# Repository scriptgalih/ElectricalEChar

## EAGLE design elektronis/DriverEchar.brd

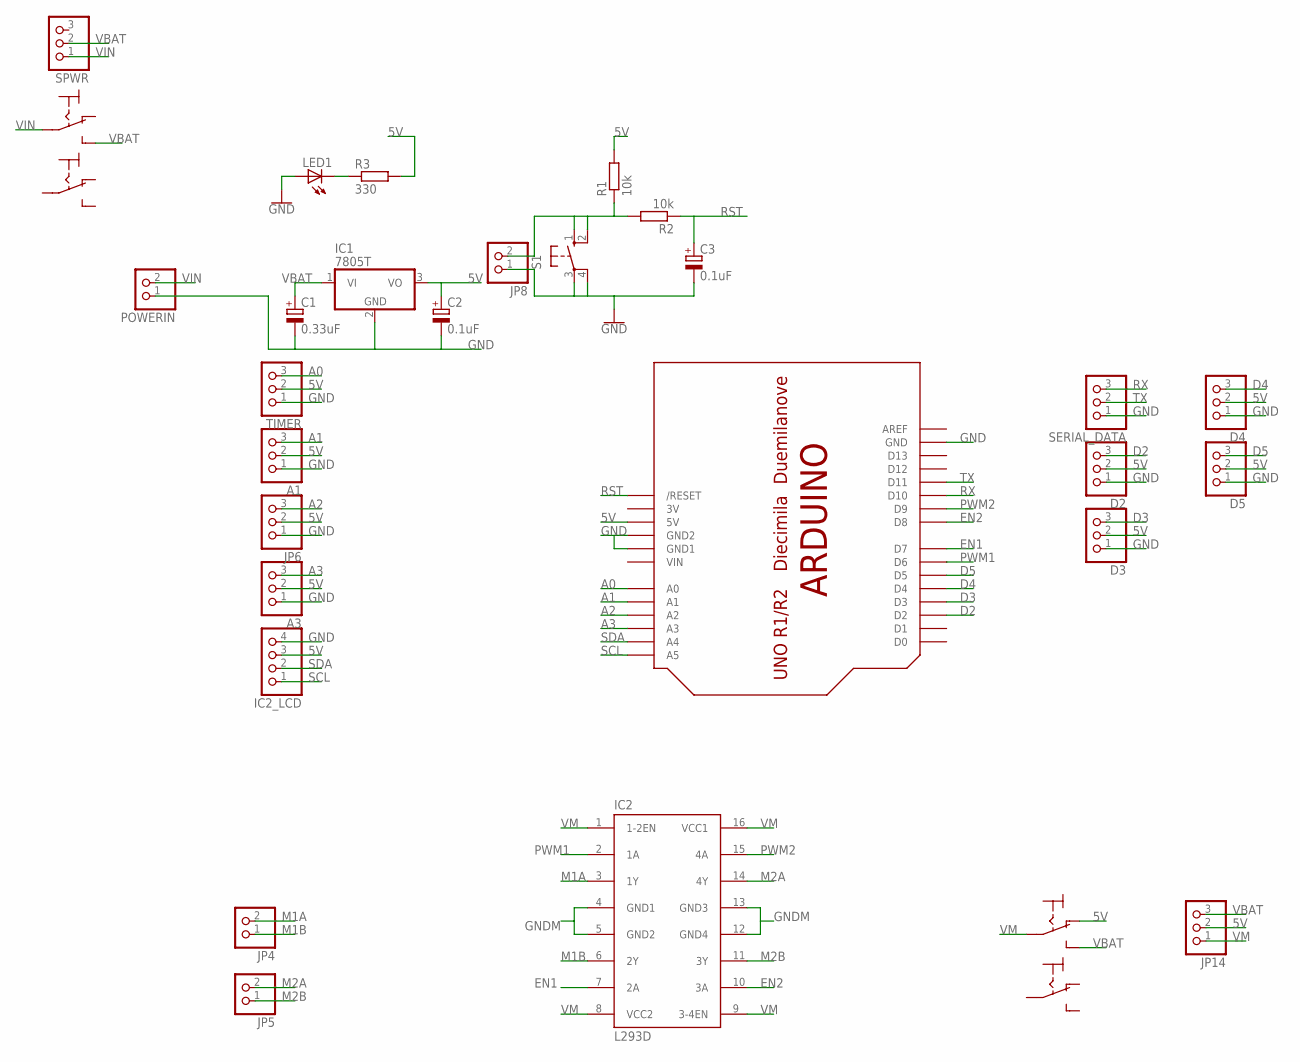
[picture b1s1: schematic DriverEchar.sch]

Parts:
A1, A3: PINHD-1X3; 1X03
C1: 0.33uF; E2,5-6
C2, C3: 0.1uF; E2,5-6
D2, D3, D4, D5: PINHD-1X3; 1X03
IC1: 7805T; TO220H
IC2: L293D; DIL16
IC2_LCD: PINHD-1X4; 1X04
JP4, JP5, JP8: PINHD-1X2; 1X02
JP6, JP14: PINHD-1X3; 1X03
LED1: LED3MM
POWERIN: PINHD-1X2; 1X02
R1, R2: 10k; 0207/10
R3: 330; 0207/10
S1: 10-XX; B3F-10XX
SERIAL_DATA: PINHD-1X3; 1X03
SPWR: PINHD-1X3; 1X03
TIMER: PINHD-1X3; 1X03
U$1: ARDUINO-BPLACE
U$2, U$3: MICROSWITCH_2X3

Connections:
3V: U$1.3V
5V: A1.2, A3.2, C2.+, D2.2, D3.2, D4.2, D5.2, IC1.3 (VO), IC2_LCD.3, JP6.2, JP14.2, R1.2, R3.2, TIMER.2, U$1.5V, U$2.NC1
A0: TIMER.3, U$1.A0
A1: A1.3, U$1.A1
A2: JP6.3, U$1.A2
A3: A3.3, U$1.A3
D2: D2.3, U$1.D2
D3: D3.3, U$1.D3
D4: D4.3, U$1.D4
D5: D5.3, U$1.D5
EN1: IC2.7 (2A), U$1.D7
EN2: IC2.10 (3A), U$1.D8
GND: A1.1, A3.1, C1.-, C2.-, C3.-, D2.1, D3.1, D4.1, D5.1, IC1.2 (GND), IC2_LCD.4, JP6.1, JP8.1, LED1.A, POWERIN.1, S1.3, S1.4 (P1), SERIAL_DATA.1, TIMER.1, U$1.GND, U$1.GND1, U$1.GND2
GNDM: IC2.4 (GND1), IC2.5 (GND2), IC2.12 (GND4), IC2.13 (GND3)
M1A: IC2.3 (1Y), JP4.2
M1B: IC2.6 (2Y), JP4.1
M2A: IC2.14 (4Y), JP5.2
M2B: IC2.11 (3Y), JP5.1
unnamed: JP8.2, R1.1, R2.2, S1.1 (S), S1.2 (S1)
unnamed: LED1.K (C), R3.1
PWM1: IC2.2 (1A), U$1.D6
PWM2: IC2.15 (4A), U$1.D9
RST: C3.+, R2.1, U$1.RESET (/RESET)
RX: SERIAL_DATA.3, U$1.D10
SCL: IC2_LCD.1, U$1.A5
SDA: IC2_LCD.2, U$1.A4
TX: SERIAL_DATA.2, U$1.D11
VBAT: C1.+, IC1.1 (VI), JP14.3, SPWR.2, U$2.NO1, U$3.NO1
VIN: POWERIN.2, SPWR.1, U$1.VIN, U$3.C1 (COM1)
VM: IC2.1 (1-2EN), IC2.8 (VCC2), IC2.9 (3-4EN), IC2.16 (VCC1), JP14.1, U$2.C1 (COM1)

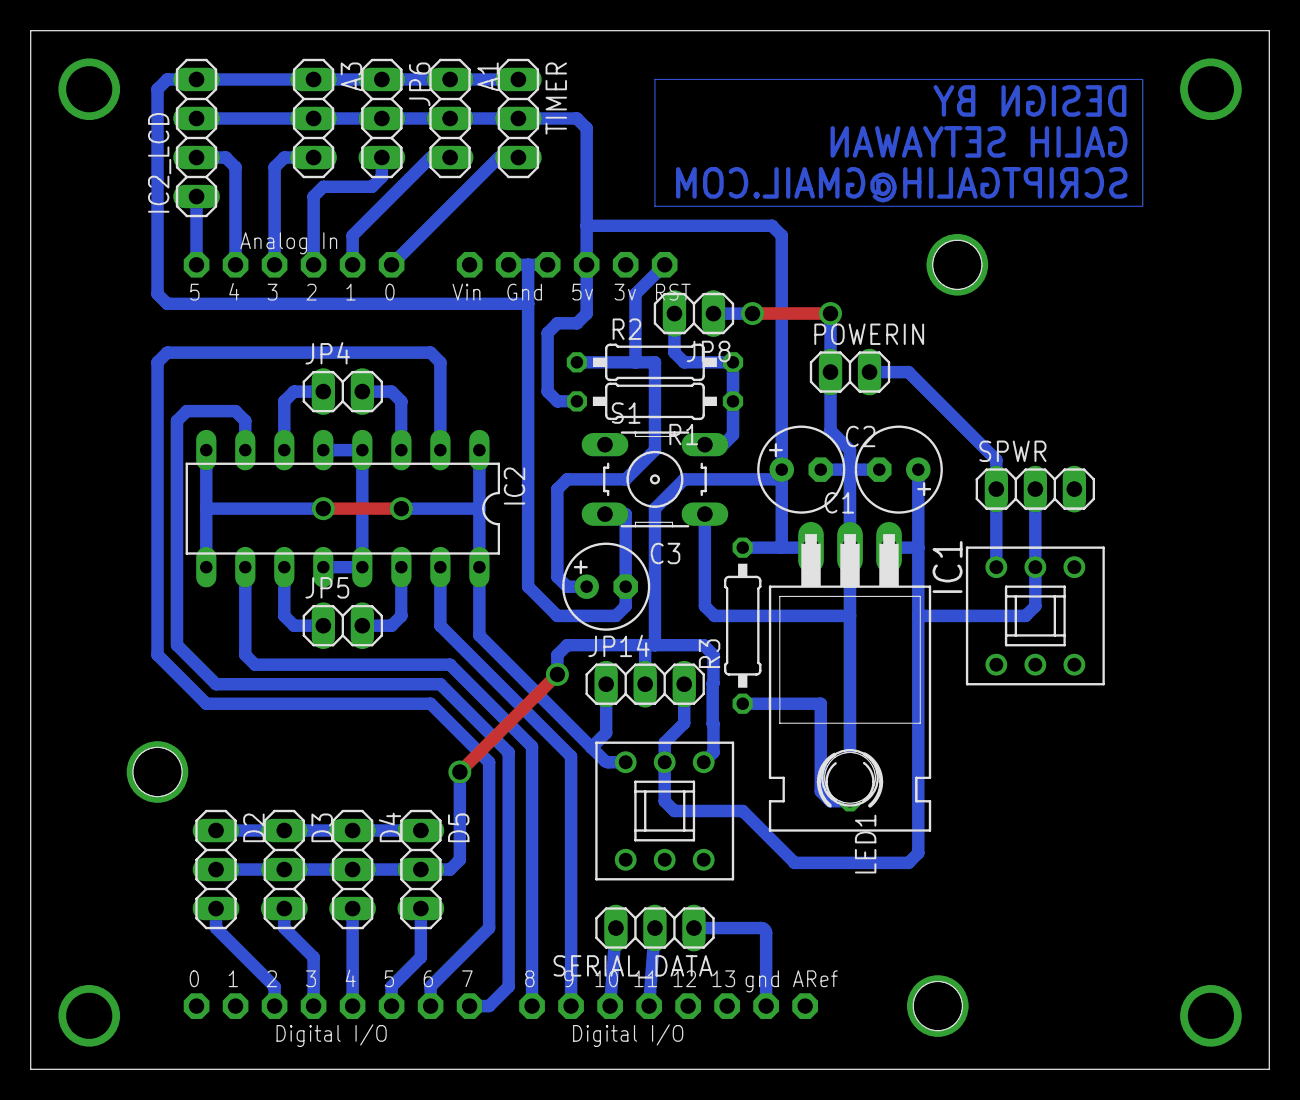
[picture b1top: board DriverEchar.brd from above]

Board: 2 copper layers, 80.6 x 67.6 mm, 29 parts (0 on the bottom side), 29 nets.

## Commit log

2019-09-21 Elektronis Echar
    membuat fitur reset, analog, RX TX, SDA SCL, Regulator 5v
2019-09-26 update komponen
    menambah tactile switch / micro switch
    pembaharuan pelabelan komponen
2019-09-27 fix jumper and pin header space

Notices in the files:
parts and their libraries:
SparkFun-PowerSymbols: Licensing: Creative Commons ShareAlike 4.0 International - https://creativecommons.org/licenses/by-sa/4.0
